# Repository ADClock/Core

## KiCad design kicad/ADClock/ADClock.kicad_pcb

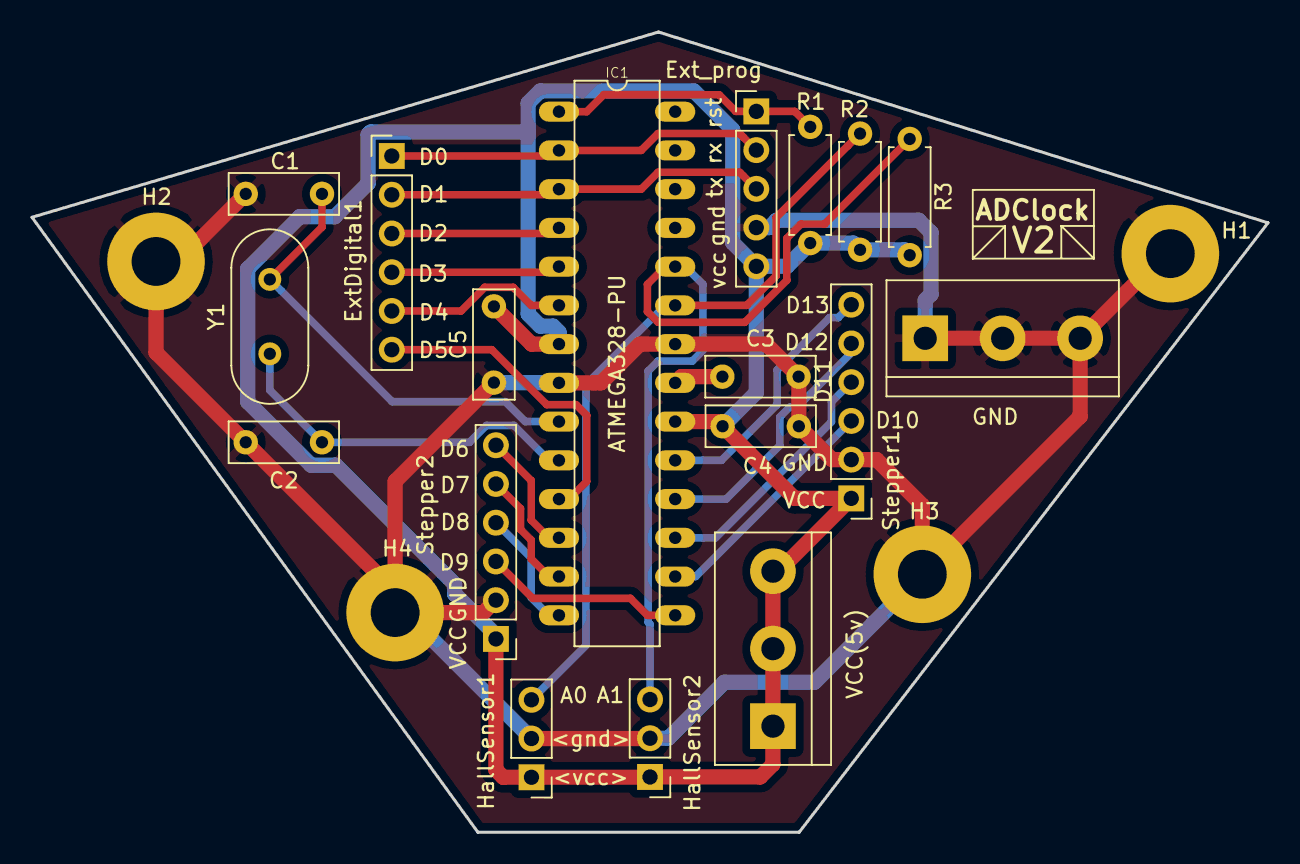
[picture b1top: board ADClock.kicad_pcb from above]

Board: 2 copper layers, 81.0 x 52.5 mm, 22 parts (0 on the bottom side), 22 nets.

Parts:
C1, C2, C3, C4, C5: C; C_Rect_L7.0mm_W2.5mm_P5.00mm
ExtDigital1: Conn_Ext_digital; PinHeader_1x06_P2.54mm_Vertical
Ext_prog: Conn_Programmer; PinHeader_1x05_P2.54mm_Vertical
GND: Screw_GND; TerminalBlock_bornier-3_P5.08mm
H1, H2, H3, H4: MountingHole_Pad; MountingHole_3.2mm_M3_Pad
HallSensor1, HallSensor2: Hall_Sensor_1; PinHeader_1x03_P2.54mm_Vertical
IC1: ATMEGA328-PU; DIL28
R1, R2, R3: R; R_Axial_DIN0207_L6.3mm_D2.5mm_P7.62mm_Horizontal
Stepper1: Stepper_1; PinHeader_1x06_P2.54mm_Vertical
Stepper2: Stepper_2; PinHeader_1x06_P2.54mm_Vertical
VCC(5v): Screw_VCC; TerminalBlock_bornier-3_P5.08mm
Y1: Crystal; Crystal_HC49-4H_Vertical

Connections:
unnamed: C1.1, C2.2, C3.2, C4.2, C5.1, Ext_prog.4, GND.1, GND.2, GND.3, H1.1, H2.1, H3.1, H4.1, HallSensor1.2, HallSensor2.2, IC1.8, IC1.22, Stepper1.2, Stepper2.2
unnamed: C1.2, IC1.9, Y1.2
unnamed: C2.1, IC1.10, Y1.1
unnamed: C3.1, IC1.21
unnamed: C4.1, C5.2, Ext_prog.5, HallSensor1.1, HallSensor2.1, IC1.7, IC1.20, R1.2, R2.1, R3.1, Stepper1.1, Stepper2.1, VCC(5v).1, VCC(5v).2, VCC(5v).3
unnamed: ExtDigital1.1, Ext_prog.2, IC1.2
unnamed: ExtDigital1.2, Ext_prog.3, IC1.3
unnamed: ExtDigital1.3, IC1.4
unnamed: ExtDigital1.4, IC1.5
unnamed: ExtDigital1.5, IC1.6
unnamed: ExtDigital1.6, IC1.11
unnamed: HallSensor1.3, IC1.23, R2.2
unnamed: HallSensor2.3, IC1.24, R3.2
unnamed: Ext_prog.1, IC1.1, R1.1
unnamed: IC1.12, Stepper2.6
unnamed: IC1.13, Stepper2.5
unnamed: IC1.14, Stepper2.4
unnamed: IC1.15, Stepper2.3
unnamed: IC1.16, Stepper1.3
unnamed: IC1.17, Stepper1.4
unnamed: IC1.18, Stepper1.5
unnamed: IC1.19, Stepper1.6

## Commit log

2019-05-18 Init
2019-05-18 PlatformIO Code
2019-05-18 Deleted settings.json
2019-05-18 edited envs & gitignore
2019-05-18 Added simple data communication
2019-05-18 Updated .gitignore
2019-05-18 Deleted 794a65dd73a95240
2019-05-18 Motor class implementation
2019-05-18 model updates
2019-05-18 Motor Calibration & Cooldown
2019-05-18 commands draft
2019-05-19 board changes
2019-05-21 added second motor calibration
2019-05-21 simple data communikation
2019-05-21 stupid merge
2019-05-21 hall pullup
2019-05-21 new communication test
2019-05-21 täst
2019-05-22 Updated commands.txt
2019-05-22 delk
2019-05-23 added shiftInShiftOut bitwise (should work)
2019-06-04 Excel mit Teilen
2019-06-04 stupid kabel i hate you c:
2019-06-05 motor calibration test
2019-06-06 some more fixes
2019-06-06 Little fix data communication
2019-06-06 Fixed main.cpp
2019-06-06 added some degree
2019-06-09 improved data communication
2019-06-10 small improvements for data sending
2019-06-10 improved data communication speed alot
2019-06-11 deleted old data communication
2019-06-11 few more tests
2019-06-11 added delays. Coz data is slow!
2019-06-11 fixed some timer
2019-06-11 let it work
2019-06-12 created some code for bigboy
2019-06-12 changing names
2019-06-12 finally... Hopefully it works
2019-06-13 changed bestellung
2019-06-13 updated orders
2019-06-13 moved project
2019-06-14 added mbed
2019-06-14 1500µs für 8 byte image
2019-06-17 doing some crazy stuff
2019-06-17 improvements are always nice
2019-06-19 added basic json support
2019-06-23 calibration advancements
2019-06-23 Fixed calibration
2019-06-27 small changes
2019-06-27 removed build folder from git
2019-06-27 only send image for one clock (for testing)
2019-07-01 added some comments
2019-07-01 added some testing code
2019-07-01 tested motor step count
2019-07-02 fixed calibration command
2019-07-02 adding delay after init command (let the clocks rotate)
2019-07-02 move motor first outside the calibartion area then start calibration
2019-07-02 little fix?
2019-07-02 changed calibration
2019-07-02 Updated Excel
2019-07-02 Updated Excel again
2019-07-21 added Http-Server with basic requests
2019-07-21 even more magic (HTTP-REST-API workin pretty well) (took no time)
2019-07-22 Deleted 1b06001b5096ddd4
2019-07-22 Set up CI with Azure Pipelines
    [skip ci]
2019-07-22 Deleted azure-pipelines.yml
2019-09-08 pushed some changes from my laptop
2019-09-08 changed cpp props
2019-09-08 deleted old project
2019-09-09 Corrected for two clocks
2019-09-09 added some debug messages
2019-09-09 added debug message
2019-09-09 <= 0 :-)
2019-09-27 changed calibration (hopefully fixed it?)
2019-09-27 added Motormanager added Config.h changed deserialisation splitted deserialisation and motor set next pos
2019-09-28 added debug
2019-09-29 fixed everything its workin :-) ardunio > changed calibration (splitted into calibrationsteps) > changed motormanager > fixed delays in InputStream > added Debug messages
    bigboy/stm
    > added manager
    > changed button behavior
    > added Config
    > added DEBUG-Flag
    > added Testflag for less clocks
2019-09-29 added shitty speedtests
2019-10-03 added speedcheck
2019-10-05 v2 working Alles geflasht dann probiert. Es hat funktioniert! Genau so wie es ist!
2019-10-09 current version
2019-11-09 somtimes commits are bigger
2019-12-03 not working #part 1 communication esp stm
2019-12-03 added new project... please git
2019-12-04 pushed some not workin code
2019-12-05 did some shit
2019-12-08 now its workin i think
2019-12-09 completed rest api
2019-12-10 well sometimes you have to make changes
2019-12-13 working version
2019-12-19 some fixes
2019-12-21 some almost workin code love it
2019-12-21 Fffed some strings
2019-12-21 added html landing page...
2019-12-22 arduino code cleanup
2019-12-22 not wkrin
2019-12-22 communication almost stable
2019-12-22 non working wifi ap stuff... :(
2019-12-22 pushed some more unfinished code
2019-12-23 started cleanup of request manager
2019-12-26 sometimes you have to fix Buffer :)
2019-12-27 fixed double init on esp start
2019-12-27 fixed data communication? i dont think so :(
2019-12-27 changed fast instable HttpServer to slow stable WebServer
2019-12-27 slight performance boost on file sending
2019-12-30 added speedtest
2020-01-15 hoefully it doenst break anything
2020-01-17 get the 6 clocks running
2020-01-18 well its workin better and better i guess
2020-01-20 I changed nothing... But there must me changes anywhere
2020-01-20 prepare for presentation
2020-01-20 smoother current time on single clock
2021-01-16 added logo
